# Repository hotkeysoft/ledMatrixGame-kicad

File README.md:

# LED Matrix Game
Rev A October 2019

### Handheld Electronic Game
- ATmega328PB microcontroller running at 12MHz
- 53 LEDs
- 6 push buttons
- Buzzer
- Tag-Connect for programming
- Runs on 3 AAA batteries

The microcontroller runs a [TMS1000-series emulator](https://github.com/hotkeysoft/emulators) I made.

The Split Second game (by *Parker Brothers*) TMS1400 ROM is loaded on the emulator.

Images
============
|Front                                                 | Back                                              |
|------------------------------------------------------|---------------------------------------------------|
|||

### Schematics (pdf)
- [Complete schematics](./img/schema.pdf)

### PCB Images (svg)
- [Top](./img/pcb-front.svg)
- [Bottom](./img/pcb-back.svg)

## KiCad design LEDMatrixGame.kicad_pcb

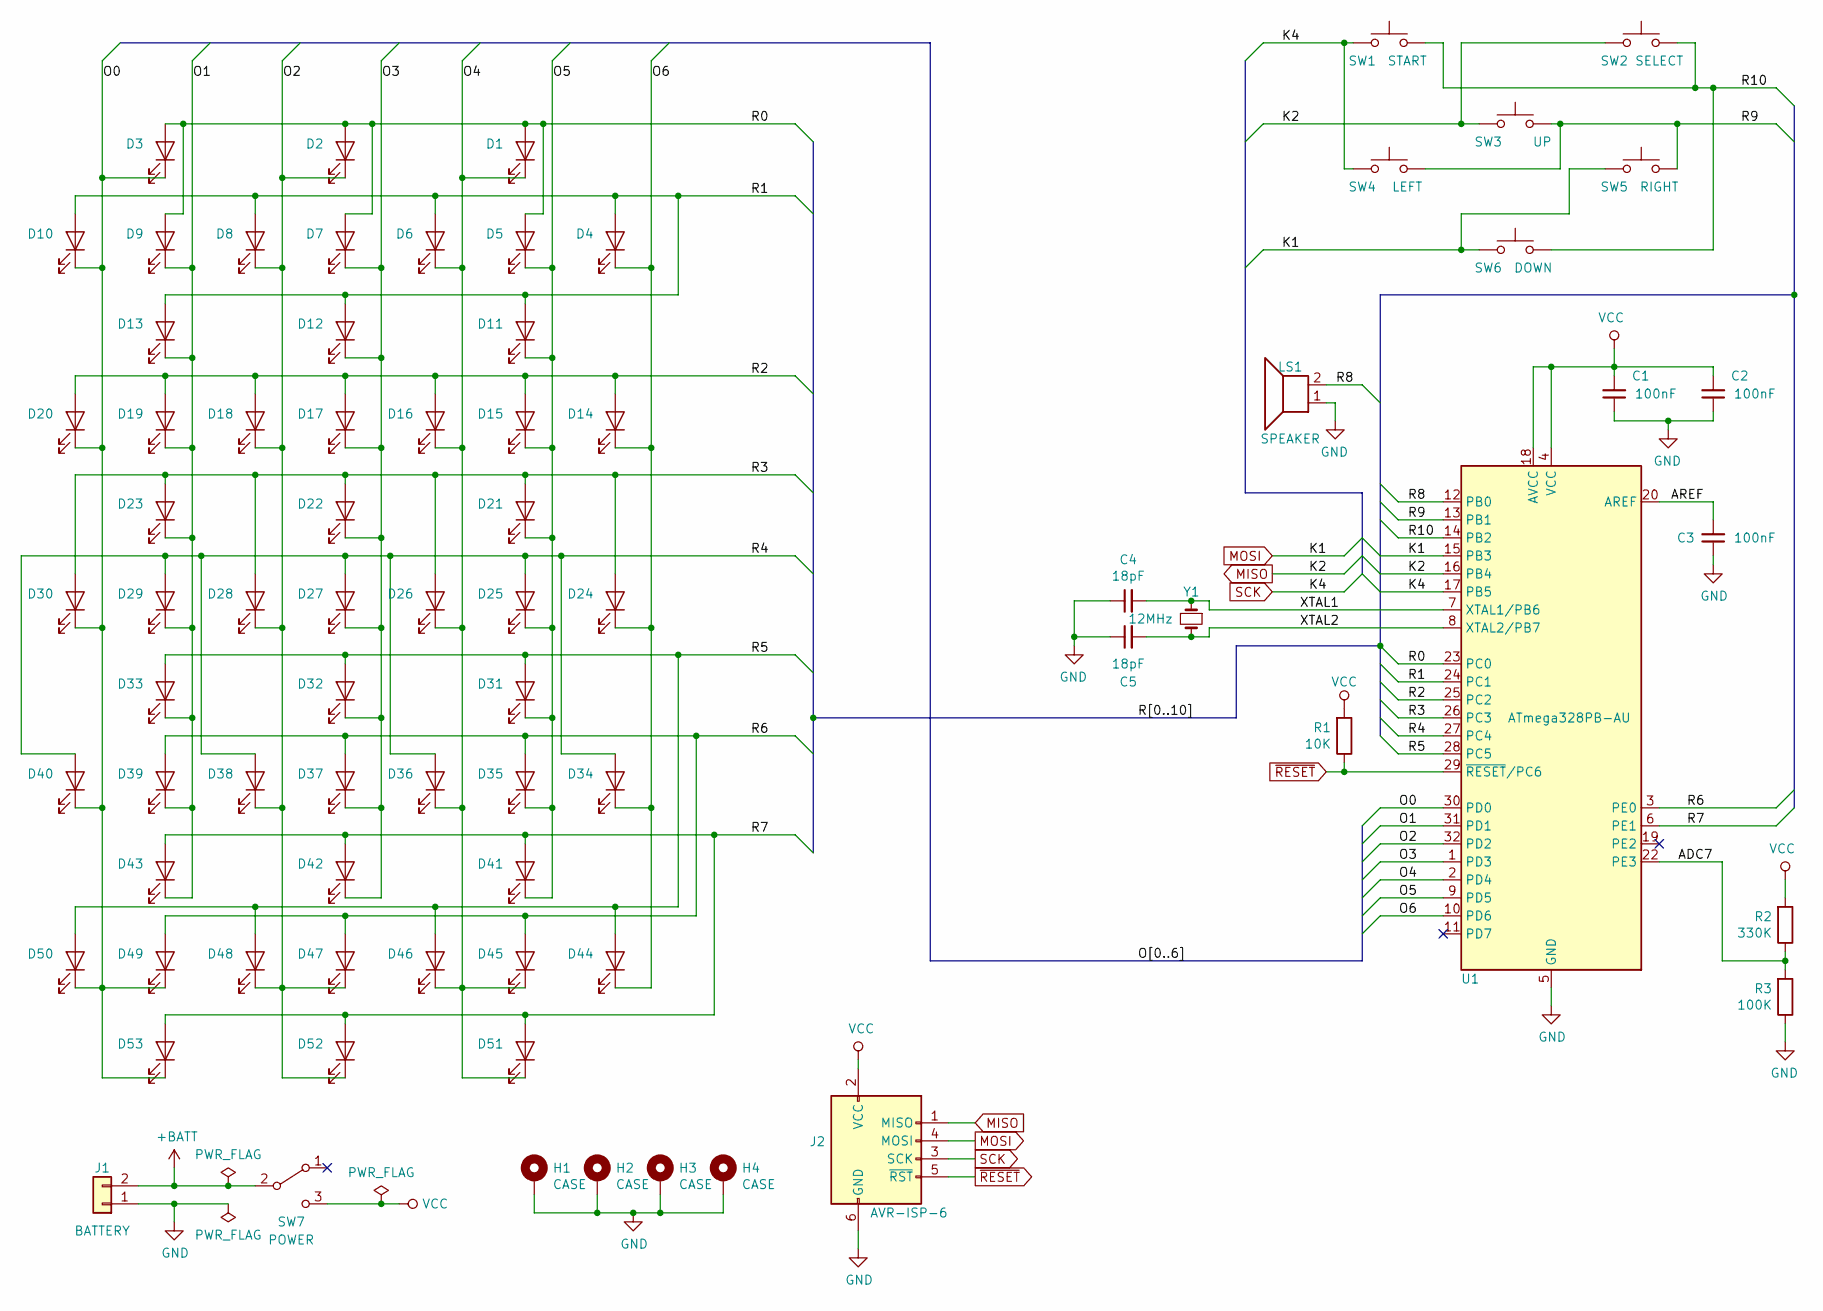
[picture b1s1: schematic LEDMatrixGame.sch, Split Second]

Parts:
C1, C2, C3: 100nF; C_0805_2012Metric_Pad1.15x1.40mm_HandSolder
C4, C5: 18pF; C_0805_2012Metric_Pad1.15x1.40mm_HandSolder
D1, D2, D3, D4, D6, D8, D10, D11, D12, D13, D14, D16, D18, D20, D21, D22, D23, D24, D26, D28, D30, D31, D32, D33, D34, D36, D38, D40, D41, D42, D43, D44, D46, D48, D50, D51, D52, D53: LED_Rectangular_W5.0mm_H2.0mm
D5, D7, D9, D15, D17, D19, D25, D27, D29, D35, D37, D39, D45, D47, D49: LED_D3.0mm
H1, H2, H3, H4: CASE; MountingHole_2.5mm_Pad
J1: BATTERY; PinHeader_1x02_P2.54mm_Vertical
J2: AVR-ISP-6; Tag-Connect_TC2030-IDC-NL_2x03_P1.27mm_Vertical
LS1: SPEAKER; PinHeader_1x02_P2.54mm_Vertical
R1: 10K; R_0805_2012Metric_Pad1.15x1.40mm_HandSolder
R2: 330K; R_0805_2012Metric_Pad1.15x1.40mm_HandSolder
R3: 100K; R_0805_2012Metric_Pad1.15x1.40mm_HandSolder
SW1: START; SW_PUSH_6mm_H5mm
SW2: SELECT; SW_PUSH_6mm_H5mm
SW3: UP; SW_PUSH_6mm_H5mm
SW4: LEFT; SW_PUSH_6mm_H5mm
SW5: RIGHT; SW_PUSH_6mm_H5mm
SW6: DOWN; SW_PUSH_6mm_H5mm
SW7: POWER; SW_CuK_OS102011MA1QN1_SPDT_Angled
U1: ATmega328PB-AU; TQFP-32_7x7mm_P0.8mm
Y1: 12MHz; Crystal_HC49-4H_Vertical

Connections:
+BATT: J1.2, SW7.2 (B)
/ADC7: R2.1, R3.2, U1.22 (PE3)
/AREF: C3.2, U1.20 (AREF)
/O0: D3.1 (K), D10.1 (K), D20.1 (K), D30.1 (K), D40.1 (K), D49.1 (K), D50.1 (K), D53.1 (K), U1.30 (PD0)
/O1: D9.1 (K), D13.1 (K), D19.1 (K), D23.1 (K), D29.1 (K), D33.1 (K), D39.1 (K), D43.1 (K), U1.31 (PD1)
/O2: D2.1 (K), D8.1 (K), D18.1 (K), D28.1 (K), D38.1 (K), D47.1 (K), D48.1 (K), D52.1 (K), U1.32 (PD2)
/O3: D7.1 (K), D12.1 (K), D17.1 (K), D22.1 (K), D27.1 (K), D32.1 (K), D37.1 (K), D42.1 (K), U1.1 (PD3)
/O4: D1.1 (K), D6.1 (K), D16.1 (K), D26.1 (K), D36.1 (K), D45.1 (K), D46.1 (K), D51.1 (K), U1.2 (PD4)
/O5: D5.1 (K), D11.1 (K), D15.1 (K), D21.1 (K), D25.1 (K), D31.1 (K), D35.1 (K), D41.1 (K), U1.9 (PD5)
/O6: D4.1 (K), D14.1 (K), D24.1 (K), D34.1 (K), D44.1 (K), U1.10 (PD6)
/R0: D1.2 (A), D2.2 (A), D3.2 (A), D5.2 (A), D7.2 (A), D9.2 (A), U1.23 (PC0)
/R1: D4.2 (A), D6.2 (A), D8.2 (A), D10.2 (A), D11.2 (A), D12.2 (A), D13.2 (A), U1.24 (PC1)
/R2: D14.2 (A), D15.2 (A), D16.2 (A), D17.2 (A), D18.2 (A), D19.2 (A), D20.2 (A), U1.25 (PC2)
/R3: D21.2 (A), D22.2 (A), D23.2 (A), D24.2 (A), D26.2 (A), D28.2 (A), D30.2 (A), U1.26 (PC3)
/R4: D25.2 (A), D27.2 (A), D29.2 (A), D34.2 (A), D36.2 (A), D38.2 (A), D40.2 (A), U1.27 (PC4)
/R5: D31.2 (A), D32.2 (A), D33.2 (A), D44.2 (A), D46.2 (A), D48.2 (A), D50.2 (A), U1.28 (PC5)
/R6: D35.2 (A), D37.2 (A), D39.2 (A), D45.2 (A), D47.2 (A), D49.2 (A), U1.3 (PE0)
/R7: D41.2 (A), D42.2 (A), D43.2 (A), D51.2 (A), D52.2 (A), D53.2 (A), U1.6 (PE1)
/R8: LS1.2, U1.12 (PB0)
/R9: SW3.2, SW4.2, SW5.2, U1.13 (PB1)
/R10: SW1.2, SW2.2, SW6.2, U1.14 (PB2)
/XTAL1: C4.2, U1.7 (XTAL1/PB6), Y1.1
/XTAL2: C5.2, U1.8 (XTAL2/PB7), Y1.2
GND: C1.1, C2.1, C3.1, C4.1, C5.1, H1.1, H2.1, H3.1, H4.1, J1.1, J2.6 (GND), LS1.1, R3.1, U1.5 (GND), U1.21 (GND)
MISO: J2.1 (MISO), SW2.1, SW3.1, U1.16 (PB4)
MOSI: J2.4 (MOSI), SW5.1, SW6.1, U1.15 (PB3)
SCK: J2.3 (SCK), SW1.1, SW4.1, U1.17 (PB5)
VCC: C1.2, C2.2, J2.2 (VCC), R1.2, R2.2, SW7.3 (C), U1.4 (VCC), U1.18 (AVCC)
~RESET: J2.5 (~RST), R1.1, U1.29 (~RESET~/PC6)

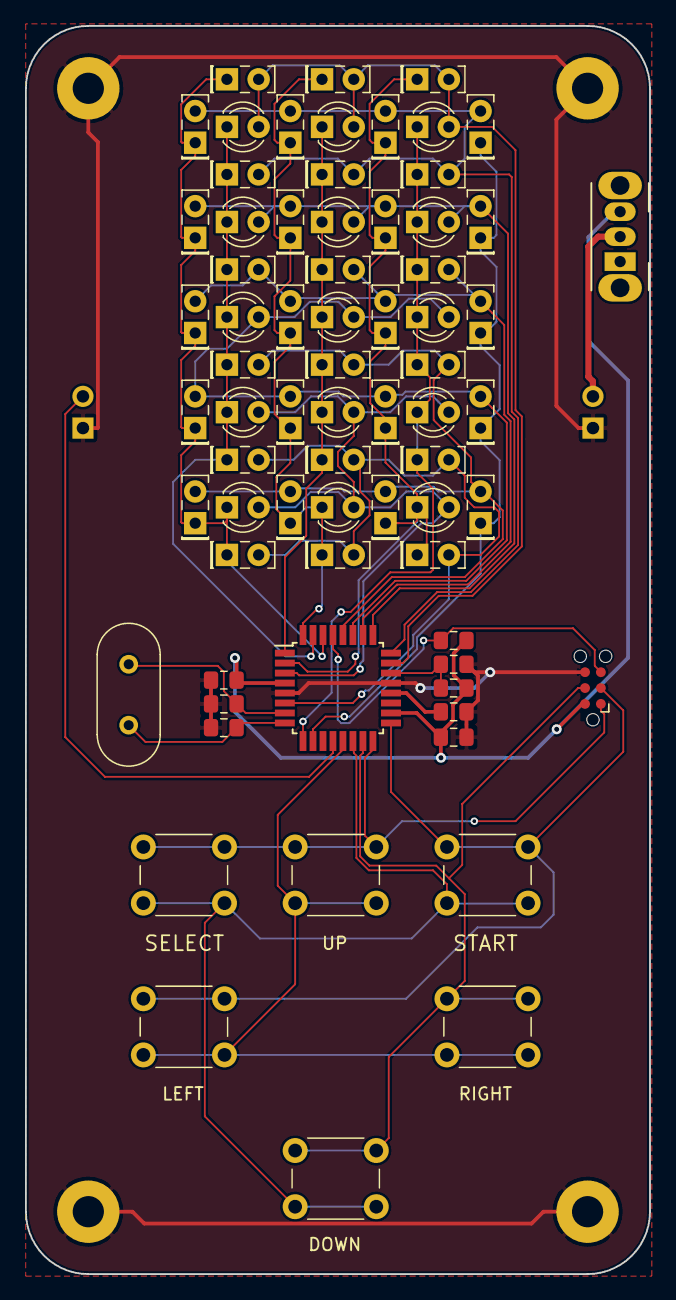
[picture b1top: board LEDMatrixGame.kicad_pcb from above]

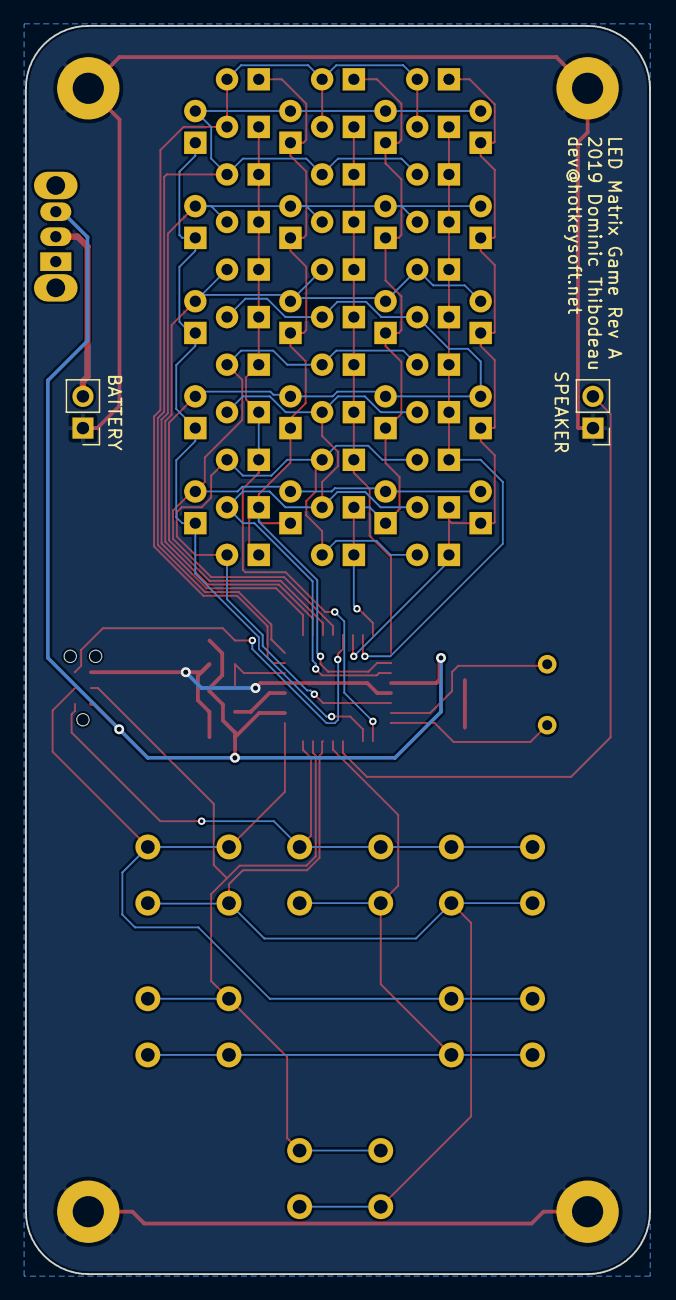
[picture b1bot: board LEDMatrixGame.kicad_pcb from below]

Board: 2 copper layers, 50.0 x 100.0 mm, 77 parts (2 on the bottom side), 29 nets.

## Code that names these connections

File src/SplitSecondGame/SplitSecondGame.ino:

#include "rom.h"
#include "TMS1000.h"

#define K1 PIN_PB3
#define K2 PIN_PB4
#define K4 PIN_PB5

#define O0 PIN_PD0
#define O1 PIN_PD1
#define O2 PIN_PD2
#define O3 PIN_PD3
#define O4 PIN_PD4
#define O5 PIN_PD5
#define O6 PIN_PD6

#define R0 PIN_PC0
#define R1 PIN_PC1
#define R2 PIN_PC2
#define R3 PIN_PC3
#define R4 PIN_PC4
#define R5 PIN_PC5
#define R6 PIN_PE0
#define R7 PIN_PE1

const int RPins[] = { R0, R1, R2, R3, R4, R5, R6, R7 };

// Buzzer
#define R8 PIN_PB0

// Buttons
#define R9 PIN_PB1
#define R10 PIN_PB2

// Buttons connected to K1-K4
void inputKCallback() {
      TMS1000::g_cpu.K = ((PINB & 56) ^ 56) >> 3;
}

// LED array connected to R0-R7
// Buzzer connected to R8
// Keypad connected do R9 R10
void outputRCallback(TMS1000::BYTE pin, bool state) {
  switch (pin) {
    case 0: case 1: case 2: case 3:
    case 4: case 5: case 6: case 7:
      digitalWrite(RPins[pin], state);      
    break;
    case 8:
      digitalWrite(R8, state);
      break;
     case 9:
      digitalWrite(R9, !state);     
      break;
     case 10:
     digitalWrite(R10, !state);
    break;
  }
}

// R = LED Anode
// O = LED Cathode
// Ox = 0 to turn on LED
const uint8_t oMap[] = {
  0b11111111, // 0
  0b11111110, // 1
  0b11111101, // 2
  0b11111011, // 3
  0b11110111, // 4
  0b11101111, // 5
  0b11011111, // 6
  0b10111111, // 7
};

void outputOCallback(TMS1000::BYTE val) {
  if (val > 0)
  {
    PORTD = oMap[val & 7];
  }
  else 
  {
    PORTD = 0b11111111;
  }
}

void setup() {
  pinMode(K1, INPUT_PULLUP);
  pinMode(K2, INPUT_PULLUP);
  pinMode(K4, INPUT_PULLUP);

  pinMode(R0, OUTPUT);
  pinMode(R1, OUTPUT);
  pinMode(R2, OUTPUT);
  pinMode(R3, OUTPUT);
  pinMode(R4, OUTPUT);
  pinMode(R5, OUTPUT);
  pinMode(R6, OUTPUT);  
  pinMode(R7, OUTPUT);  

  pinMode(R8, OUTPUT);
  pinMode(R9, OUTPUT);
  pinMode(R10, OUTPUT);

  pinMode(O0, OUTPUT);
  pinMode(O1, OUTPUT);
  pinMode(O2, OUTPUT);
  pinMode(O3, OUTPUT);
  pinMode(O4, OUTPUT);
  pinMode(O5, OUTPUT);
  pinMode(O6, OUTPUT);    
   
  TMS1000::Init(TMS1000::CPU_TMS1400, 4096, 128); 
  TMS1000::SetInputKCallback(inputKCallback);
  TMS1000::SetOutputOCallback(outputOCallback);
  TMS1000::SetOutputRCallback(outputRCallback);
  TMS1000::g_memory.ROM = rom;
  TMS1000::Reset();
}

void loop() {
  TMS1000::Step();
  delayMicroseconds(10);
}

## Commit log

2019-10-27 Import
2019-10-28 Routing, plot
2019-10-28 Added source
2021-06-27 Fix mappings
2021-06-27 Cleanup
2021-06-27 Cleanup, add images
2021-06-27 Create LICENSE
